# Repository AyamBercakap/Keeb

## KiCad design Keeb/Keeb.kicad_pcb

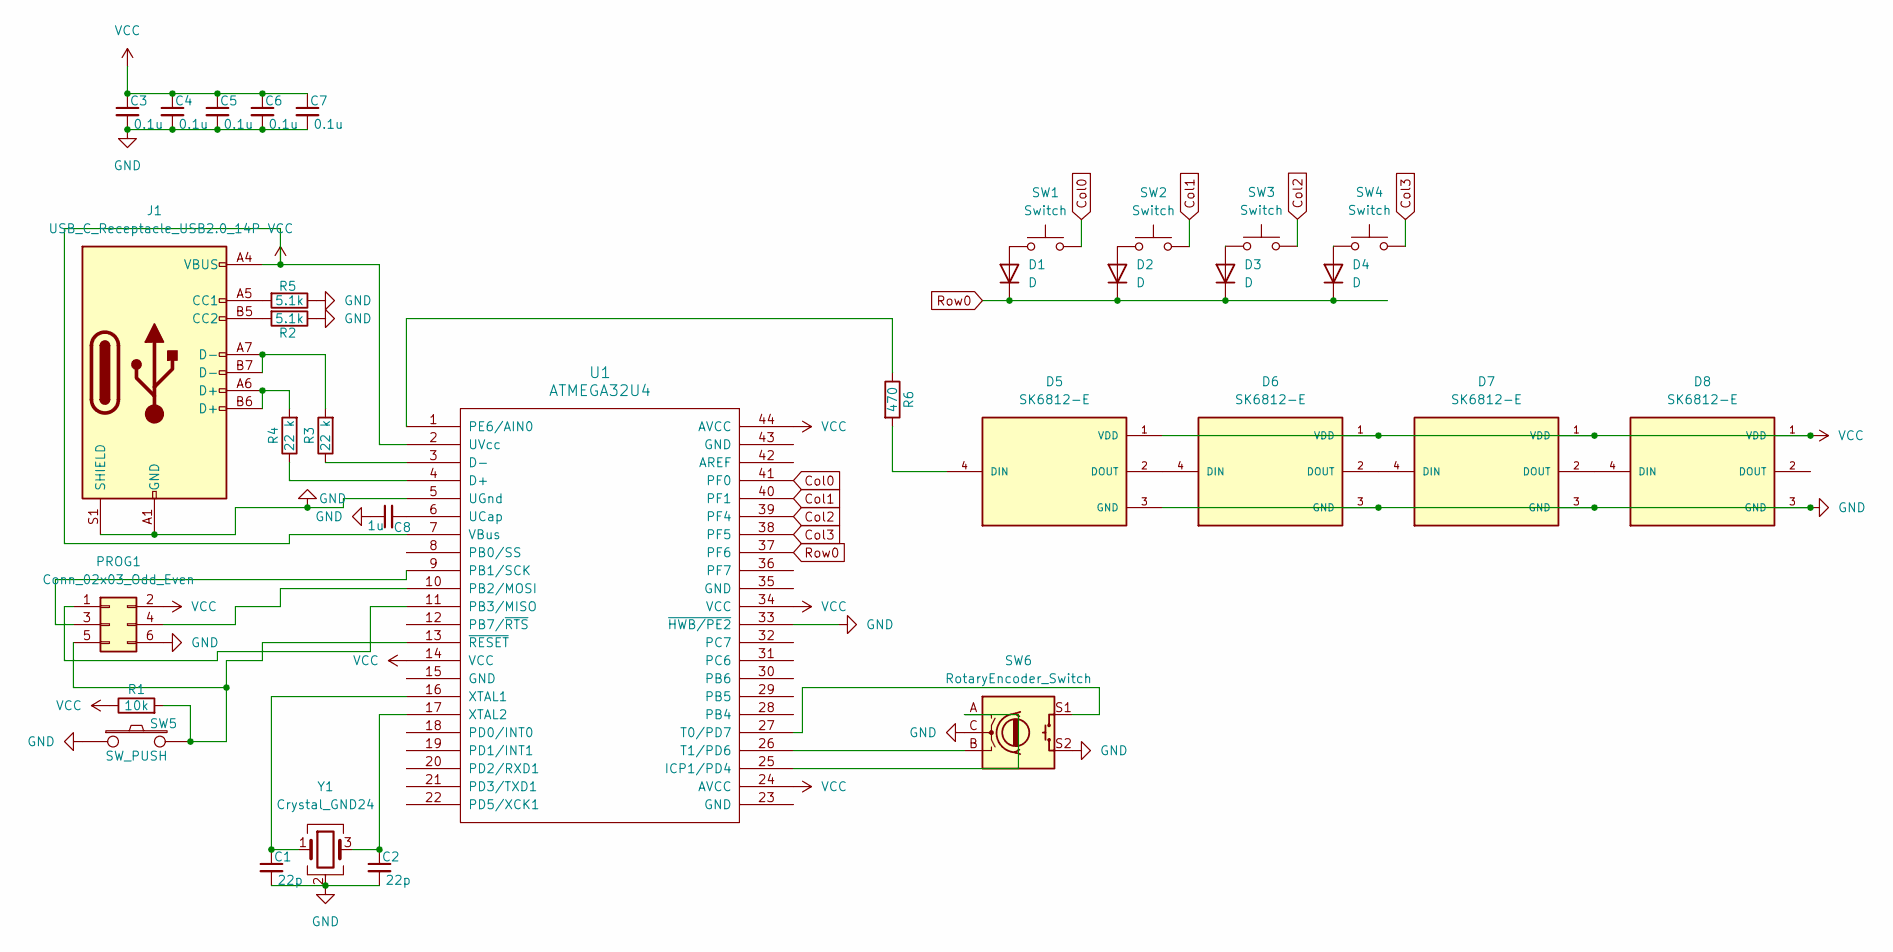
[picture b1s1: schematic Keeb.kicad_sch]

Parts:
C1, C2: 22p; C_0805_2012Metric_Pad1.18x1.45mm_HandSolder
C3, C4, C5, C6, C7: 0.1u; C_0805_2012Metric_Pad1.18x1.45mm_HandSolder
C8: 1u; C_0805_2012Metric_Pad1.18x1.45mm_HandSolder
D1, D2, D3, D4: D; D_SOD123_axial
D5, D6, D7, D8: SK6812-E; LED_SK6812-E; PARTREV 2
J1: USB_C_Receptacle_USB2.0_14P; USB_C_Receptacle_HRO_TYPE-C-31-M-12
PROG1: Conn_02x03_Odd_Even; pads
R1: 10k; R_0805_2012Metric_Pad1.20x1.40mm_HandSolder
R2, R5: 5.1k; R_0805_2012Metric_Pad1.20x1.40mm_HandSolder
R3, R4: 22 k; R_0805_2012Metric_Pad1.20x1.40mm_HandSolder
R6: 470; R_0805_2012Metric_Pad1.20x1.40mm_HandSolder
SW1, SW2, SW3, SW4: Switch; MX_PCB_1.00u
SW5: SW_PUSH; SW_SPST_TL3342
SW6: RotaryEncoder_Switch; RotaryEncoder_Alps_EC11E-Switch_Vertical_H20mm
U1: ATMEGA32U4; TQFN-44-1EP_7x7mm_P0.5mm_EP4.7x4.7mm
Y1: Crystal_GND24; Crystal_SMD_SeikoEpson_FA238-4Pin_3.2x2.5mm_HandSoldering

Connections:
Col0: SW1.2, U1.41 (PF0)
Col1: SW2.2, U1.40 (PF1)
Col2: SW3.2, U1.39 (PF4)
Col3: SW4.2, U1.38 (PF5)
GND: C1.2, C2.2, C3.2, C4.2, C5.2, C6.2, C7.2, C8.1, D5.3 (GND), D6.3 (GND), D7.3 (GND), D8.3 (GND), J1.A1 (GND), J1.A12 (GND), J1.B1 (GND), J1.B12 (GND), J1.S1 (SHIELD), PROG1.6, R2.1, R5.1, SW5.1, SW6.C, SW6.S2, U1.5 (UGnd), U1.33 (~HWB/PE2), Y1.2 (G), Y1.4 (G)
unnamed: D1.2 (A), SW1.1
unnamed: D2.2 (A), SW2.1
unnamed: D3.2 (A), SW3.1
unnamed: D4.2 (A), SW4.1
unnamed: D5.4 (DIN), R6.2
unnamed: D5.2 (DOUT), D6.4 (DIN)
unnamed: D6.2 (DOUT), D7.4 (DIN)
unnamed: D7.2 (DOUT), D8.4 (DIN)
unnamed: J1.A5 (CC1), R5.2
unnamed: J1.B5 (CC2), R2.2
unnamed: J1.A6 (D+), J1.B6 (D+), R4.2
unnamed: J1.A7 (D-), J1.B7 (D-), R3.2
unnamed: PROG1.1, U1.11 (PB3/MISO)
unnamed: PROG1.3, U1.9 (PB1/SCK)
unnamed: PROG1.4, U1.10 (PB2/MOSI)
unnamed: PROG1.5, R1.2, SW5.2, U1.13 (~RESET)
unnamed: R4.1, U1.4 (D+)
unnamed: R3.1, U1.3 (D-)
unnamed: SW6.A, U1.25 (ICP1/PD4)
unnamed: R6.1, U1.1 (PE6/AIN0)
unnamed: SW6.S1, U1.27 (T0/PD7)
unnamed: SW6.B, U1.26 (T1/PD6)
unnamed: C8.2, U1.6 (UCap)
unnamed: C1.1, U1.16 (XTAL1), Y1.1
unnamed: C2.1, U1.17 (XTAL2), Y1.3
Row0: D1.1 (K), D2.1 (K), D3.1 (K), D4.1 (K), U1.37 (PF6)
VCC: C3.1, C4.1, C5.1, C6.1, C7.1, D5.1 (VDD), D6.1 (VDD), D7.1 (VDD), D8.1 (VDD), J1.A4 (VBUS), J1.A9 (VBUS), J1.B4 (VBUS), J1.B9 (VBUS), PROG1.2, R1.1, U1.2 (UVcc), U1.7 (VBus), U1.14 (VCC), U1.24 (AVCC), U1.34 (VCC), U1.44 (AVCC)

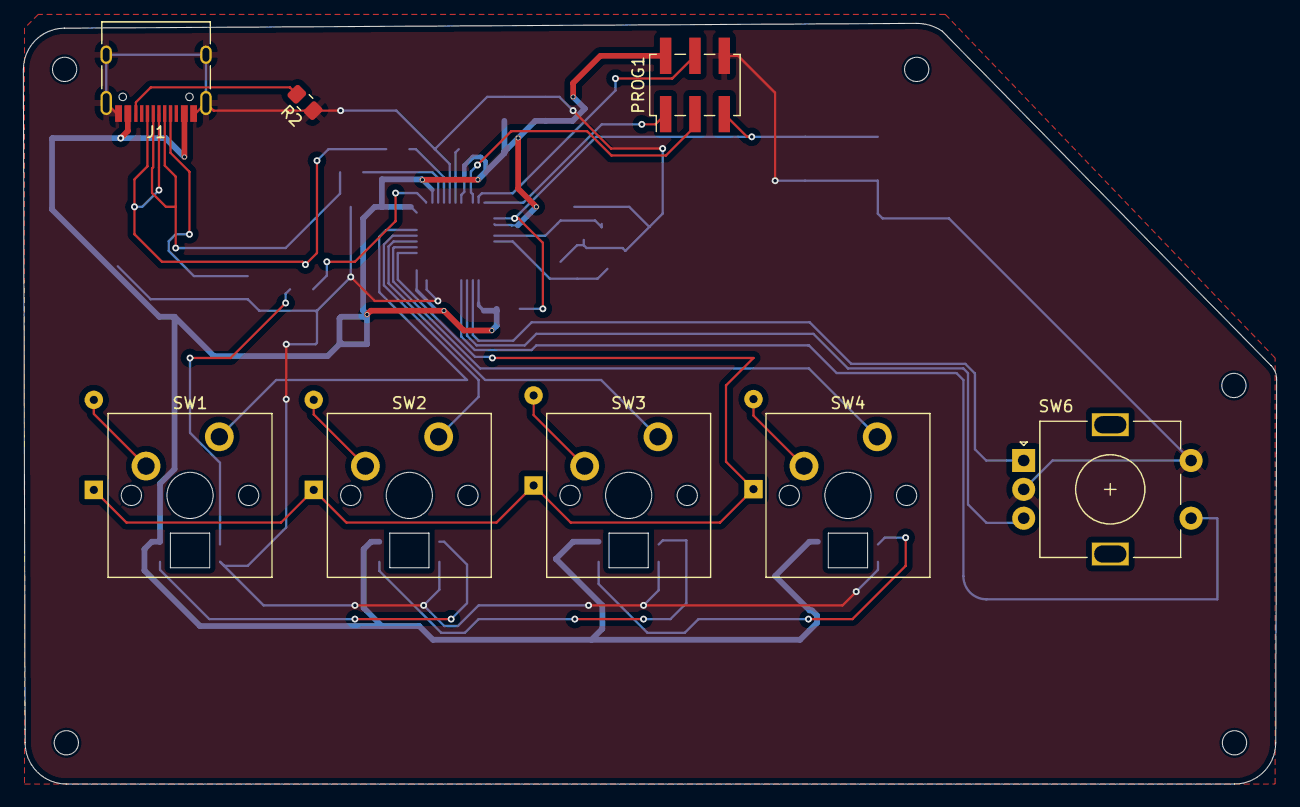
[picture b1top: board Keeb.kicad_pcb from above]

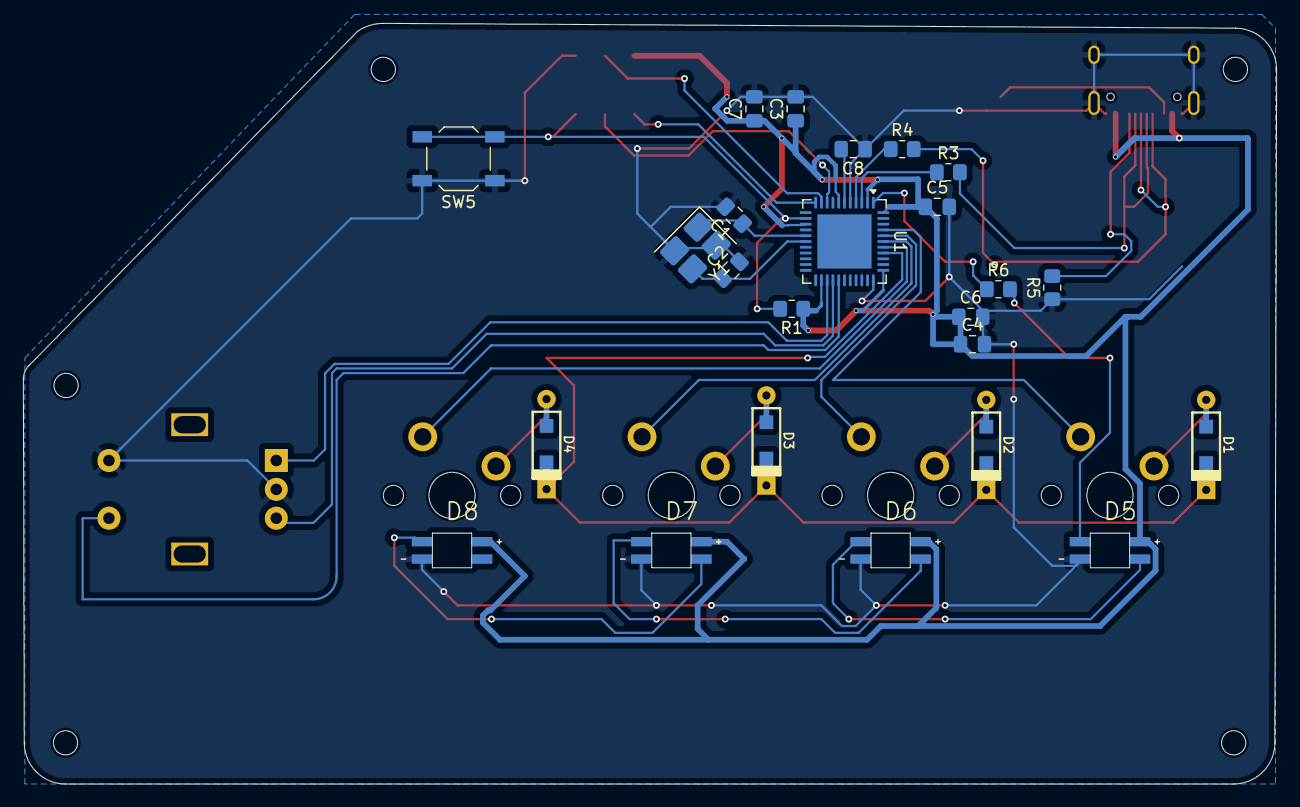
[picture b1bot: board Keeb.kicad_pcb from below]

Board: 2 copper layers, 108.6 x 65.9 mm, 32 parts (24 on the bottom side), 32 nets.

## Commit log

2026-02-20 Added New File
2026-02-23 schema img
2026-02-24 Create filegen
